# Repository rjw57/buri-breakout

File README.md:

# Bus breakout board for Búri microcomputer

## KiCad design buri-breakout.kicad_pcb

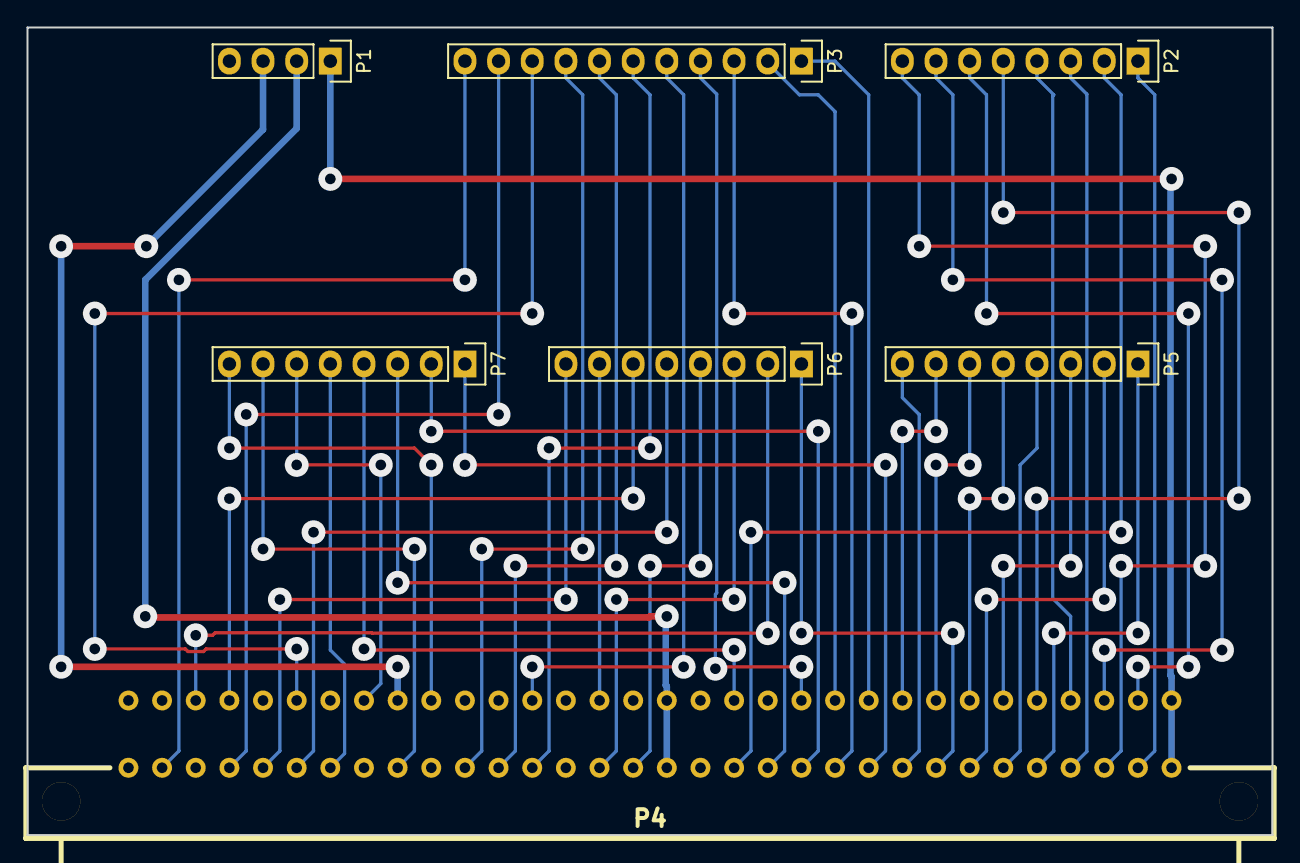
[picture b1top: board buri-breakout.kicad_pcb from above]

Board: 2 copper layers, 94.0 x 61.0 mm, 7 parts (0 on the bottom side), 47 nets.

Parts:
P1: PWR; Socket_Strip_Straight_1x04
P2: D[0..7]; Socket_Strip_Straight_1x08
P3: CTRL; Socket_Strip_Straight_1x11
P4: Buri-Bus; Budi-Bus-Male
P5: A[0..7]; Socket_Strip_Straight_1x08
P6: A[8..15]; Socket_Strip_Straight_1x08
P7: A[15..23]; Socket_Strip_Straight_1x08

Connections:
+3V3: P1.2, P4.16a, P4.16c
+5V: P1.1, P4.1a, P4.1c
/5VBat: P1.3, P4.24a
/A0: P4.5c, P5.1
/A1: P4.7c, P5.2
/A2: P4.6a, P5.3
/A3: P4.6c, P5.4
/A4: P4.7a, P5.5
/A5: P4.8a, P5.6
/A6: P4.9a, P5.7
/A7: P4.9c, P5.8
/A8: P4.8c, P6.1
/A9: P4.30a, P6.2
/A10: P4.18c, P6.3
/A11: P4.17c, P6.4
/A12: P4.27c, P6.5
/A13: P4.29a, P6.6
/A14: P4.18a, P6.7
/A15: P4.28c, P6.8
/A16: P4.10c, P7.1
/A17: P4.12c, P7.2
/A18: P4.13c, P7.3
/A19: P4.14a, P7.4
/A20: P4.26c, P7.5
/A21: P4.25a, P7.6
/A22: P4.24c, P7.7
/A23: P4.23a, P7.8
/BE: P3.2, P4.11a
/D0: P2.1, P4.2c
/D1: P2.2, P4.14c
/D2: P2.3, P4.4c
/D3: P2.4, P4.4a
/D4: P2.5, P4.5a
/D5: P2.6, P4.2a
/D6: P2.7, P4.3a
/D7: P2.8, P4.3c
/PHI2: P3.10, P4.29c
/RDY: P3.1, P4.10a
/R~W: P3.8, P4.22c
/SYNC: P3.5, P4.20a
/~IOSEL: P3.9, P4.27a
/~IRQ: P3.7, P4.21c
/~ML: P3.4, P4.12a
/~NMI: P3.6, P4.20c
/~RST: P3.11, P4.31c
/~VP: P3.3, P4.11c
GND: P1.4, P4.32a, P4.32c

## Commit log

2016-01-08 version 1
2016-01-08 add SVG plots
2016-01-08 Increase via size
2016-01-08 Re-draw PCB
2016-01-09 add README and LICENSE
